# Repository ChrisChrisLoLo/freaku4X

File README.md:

# freaku4X

A 4x10 ortho keyboard with a knob and OLED. It embraces the excess minimalism of the key count, and embraces the excess extravagence of a knob and oled screen. It also has a lower profile than your typical 4x10 orthos, since the microcontroller is facing upwards rather than downwards.

## Status
Prototyping phase. While possible to print and use right now, a few refinements can be made.
Right now, the knob button needs to be placed on the key matrix, and I would prefer to rotate the keys around so that hotswap is southfacing.

With that said, this keyboard in it's current form is usable with some amount of tinkering

## Acknowledgements
Thank you to [PCBWay](https://www.pcbway.com/) for allowing me to experiment and create wild board designs that I wouldn't be able to prototype without their support. PCBWay has always been super friendly with their service, and the quality of thier boards are great, so I do recommend using their services. The've also been supporting the custom pcb keyboard community for a while, allowing for the hobby to continue to flourish.

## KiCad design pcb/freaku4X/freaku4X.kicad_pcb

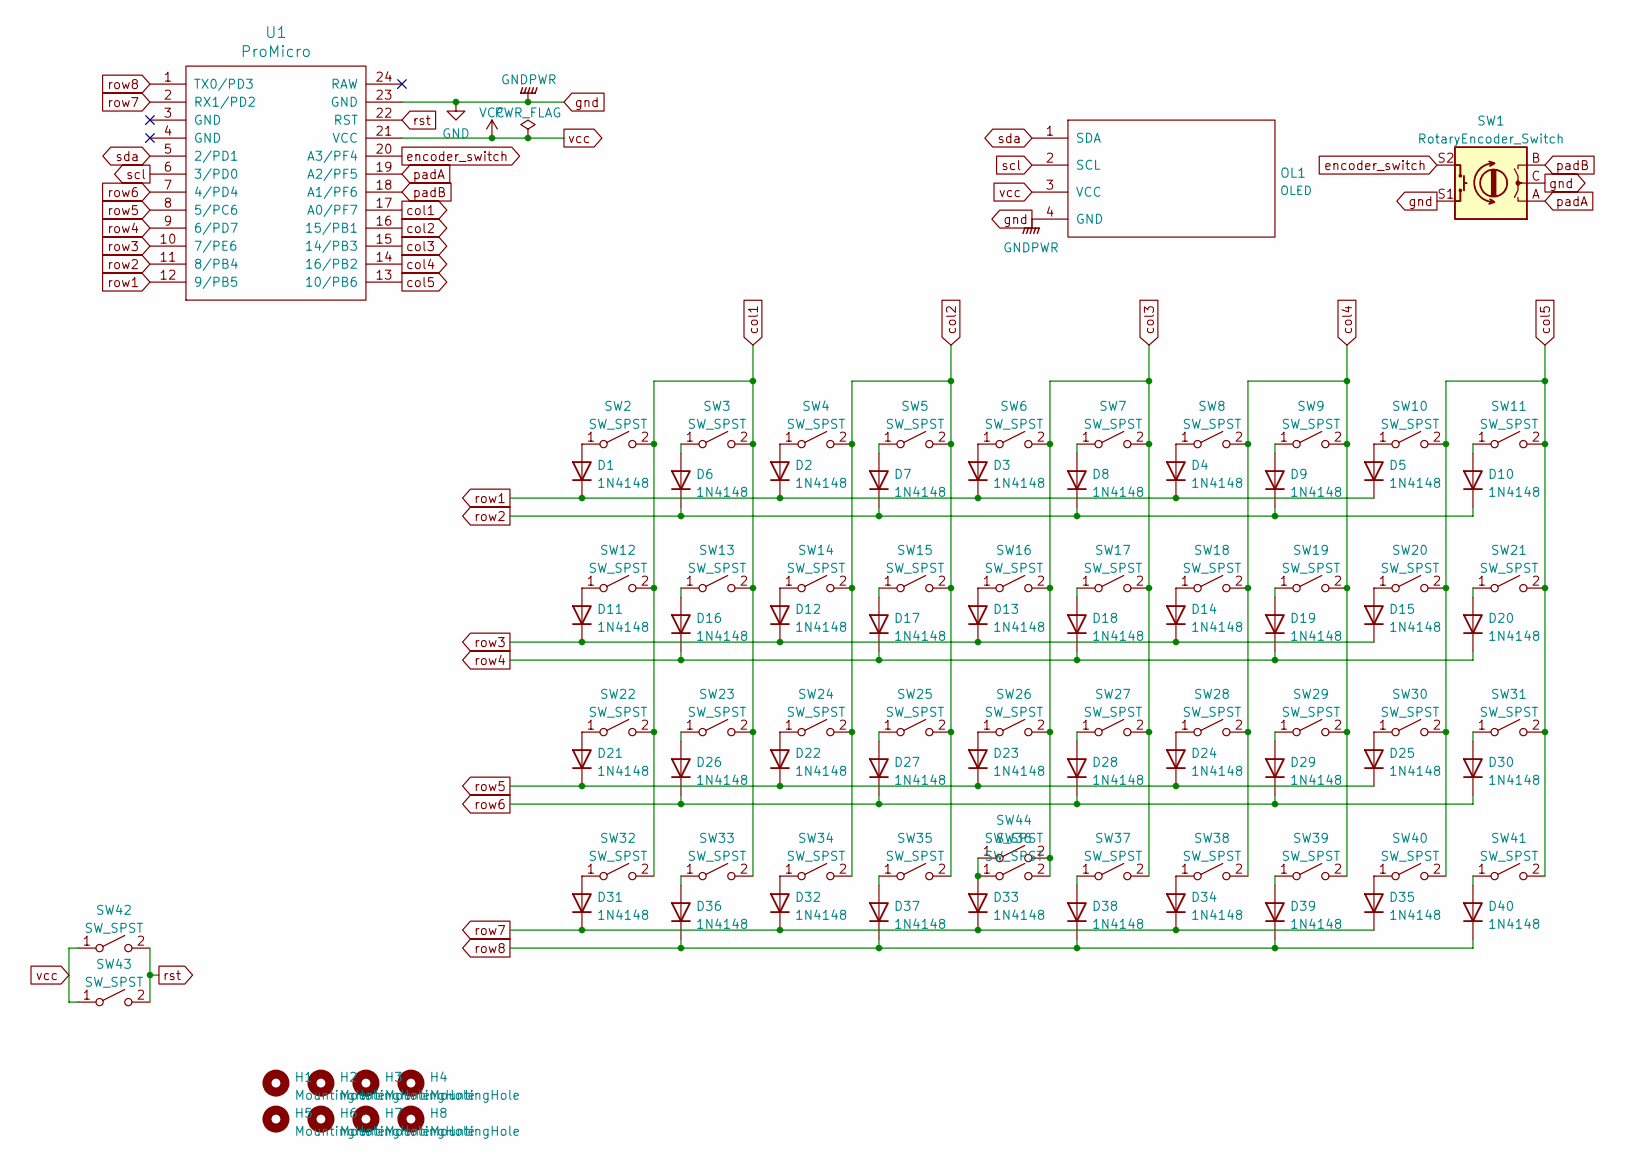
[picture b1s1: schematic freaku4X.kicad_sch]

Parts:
D1, D2, D3, D4, D5, D6, D7, D8, D9, D10, D11, D12, D13, D14, D15, D16, D17, D18, D19, D20, D21, D22, D23, D24, D25, D26, D27, D28, D29, D30, D31, D32, D33, D34, D35, D36, D37, D38, D39, D40: 1N4148
H1, H2, H3, H4, H5, H6, H7, H8: MountingHole; MountingHole_2.2mm_M2
OL1: OLED; OLED_v2
SW1: RotaryEncoder_Switch; RotaryEncoder_Alps_EC11E-Switch_Vertical_H20mm
SW2, SW3, SW4, SW5, SW6, SW7, SW8, SW9, SW10, SW11, SW12, SW13, SW14, SW15, SW16, SW17, SW18, SW19, SW20, SW21, SW22, SW23, SW24, SW25, SW26, SW27, SW28, SW29, SW30, SW31, SW32, SW33, SW34, SW35, SW36, SW37, SW38, SW39, SW40, SW41: SW_SPST; Kailh_socket_MX_optional
SW42: SW_SPST; ResetSW_4
SW43: SW_SPST; ResetSW
SW44: SW_SPST; SW_MX
U1: ProMicro; ProMicro_v3

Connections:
unnamed: D1.2 (A), SW2.1 (A)
unnamed: D2.2 (A), SW4.1 (A)
unnamed: D3.2 (A), SW6.1 (A)
unnamed: D4.2 (A), SW8.1 (A)
unnamed: D5.2 (A), SW10.1 (A)
unnamed: D6.2 (A), SW3.1 (A)
unnamed: D7.2 (A), SW5.1 (A)
unnamed: D8.2 (A), SW7.1 (A)
unnamed: D9.2 (A), SW9.1 (A)
unnamed: D10.2 (A), SW11.1 (A)
unnamed: D11.2 (A), SW12.1 (A)
unnamed: D12.2 (A), SW14.1 (A)
unnamed: D13.2 (A), SW16.1 (A)
unnamed: D14.2 (A), SW18.1 (A)
unnamed: D15.2 (A), SW20.1 (A)
unnamed: D16.2 (A), SW13.1 (A)
unnamed: D17.2 (A), SW15.1 (A)
unnamed: D18.2 (A), SW17.1 (A)
unnamed: D19.2 (A), SW19.1 (A)
unnamed: D20.2 (A), SW21.1 (A)
unnamed: D21.2 (A), SW22.1 (A)
unnamed: D22.2 (A), SW24.1 (A)
unnamed: D23.2 (A), SW26.1 (A)
unnamed: D24.2 (A), SW28.1 (A)
unnamed: D25.2 (A), SW30.1 (A)
unnamed: D26.2 (A), SW23.1 (A)
unnamed: D27.2 (A), SW25.1 (A)
unnamed: D28.2 (A), SW27.1 (A)
unnamed: D29.2 (A), SW29.1 (A)
unnamed: D30.2 (A), SW31.1 (A)
unnamed: D31.2 (A), SW32.1 (A)
unnamed: D32.2 (A), SW34.1 (A)
unnamed: D33.2 (A), SW36.1 (A), SW44.1 (A)
unnamed: D34.2 (A), SW38.1 (A)
unnamed: D35.2 (A), SW40.1 (A)
unnamed: D36.2 (A), SW33.1 (A)
unnamed: D37.2 (A), SW35.1 (A)
unnamed: D38.2 (A), SW37.1 (A)
unnamed: D39.2 (A), SW39.1 (A)
unnamed: D40.2 (A), SW41.1 (A)
col1: SW2.2 (B), SW3.2 (B), SW12.2 (B), SW13.2 (B), SW22.2 (B), SW23.2 (B), SW32.2 (B), SW33.2 (B), U1.17 (A0/PF7)
col2: SW4.2 (B), SW5.2 (B), SW14.2 (B), SW15.2 (B), SW24.2 (B), SW25.2 (B), SW34.2 (B), SW35.2 (B), U1.16 (15/PB1)
col3: SW6.2 (B), SW7.2 (B), SW16.2 (B), SW17.2 (B), SW26.2 (B), SW27.2 (B), SW36.2 (B), SW37.2 (B), SW44.2 (B), U1.15 (14/PB3)
col4: SW8.2 (B), SW9.2 (B), SW18.2 (B), SW19.2 (B), SW28.2 (B), SW29.2 (B), SW38.2 (B), SW39.2 (B), U1.14 (16/PB2)
col5: SW10.2 (B), SW11.2 (B), SW20.2 (B), SW21.2 (B), SW30.2 (B), SW31.2 (B), SW40.2 (B), SW41.2 (B), U1.13 (10/PB6)
encoder_switch: SW1.S2, U1.20 (A3/PF4)
gnd: OL1.4 (GND), SW1.C, SW1.S1, U1.23 (GND)
padA: SW1.A, U1.19 (A2/PF5)
padB: SW1.B, U1.18 (A1/PF6)
row1: D1.1 (K), D2.1 (K), D3.1 (K), D4.1 (K), D5.1 (K), U1.12 (9/PB5)
row2: D6.1 (K), D7.1 (K), D8.1 (K), D9.1 (K), D10.1 (K), U1.11 (8/PB4)
row3: D11.1 (K), D12.1 (K), D13.1 (K), D14.1 (K), D15.1 (K), U1.10 (7/PE6)
row4: D16.1 (K), D17.1 (K), D18.1 (K), D19.1 (K), D20.1 (K), U1.9 (6/PD7)
row5: D21.1 (K), D22.1 (K), D23.1 (K), D24.1 (K), D25.1 (K), U1.8 (5/PC6)
row6: D26.1 (K), D27.1 (K), D28.1 (K), D29.1 (K), D30.1 (K), U1.7 (4/PD4)
row7: D31.1 (K), D32.1 (K), D33.1 (K), D34.1 (K), D35.1 (K), U1.2 (RX1/PD2)
row8: D36.1 (K), D37.1 (K), D38.1 (K), D39.1 (K), D40.1 (K), U1.1 (TX0/PD3)
rst: SW42.2 (B), SW43.2 (B), U1.22 (RST)
scl: OL1.2 (SCL), U1.6 (3/PD0)
sda: OL1.1 (SDA), U1.5 (2/PD1)
vcc: OL1.3 (VCC), SW42.1 (A), SW43.1 (A), U1.21 (VCC)

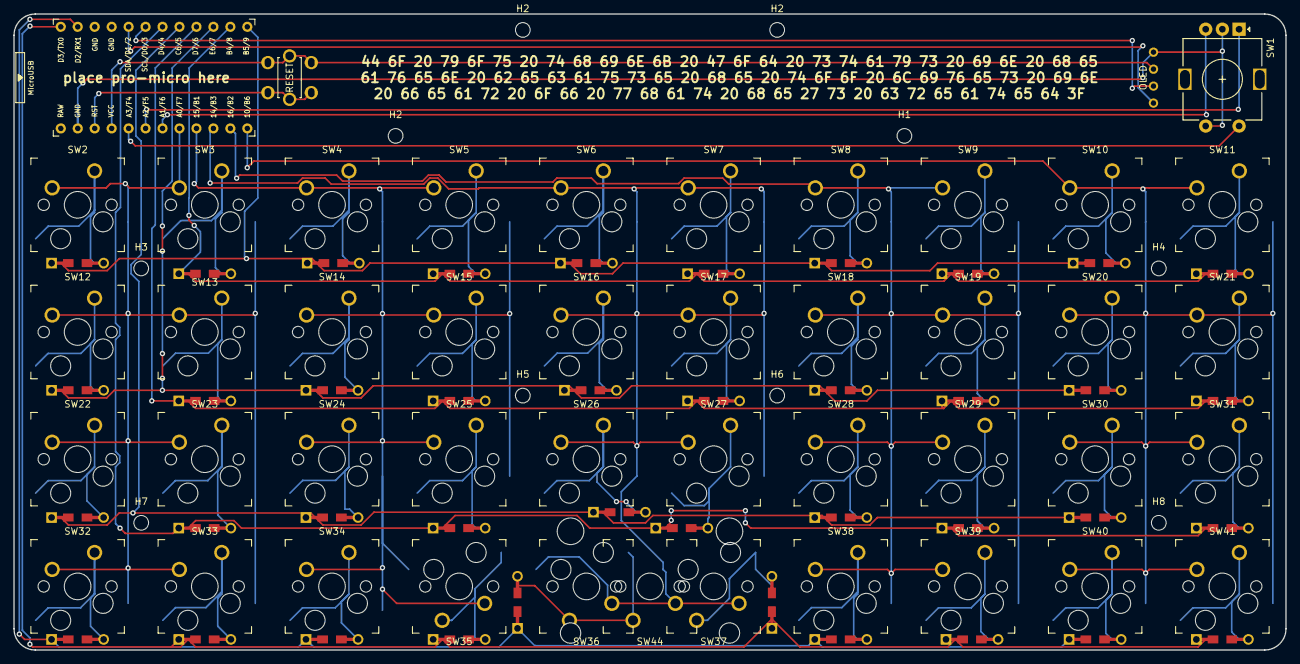
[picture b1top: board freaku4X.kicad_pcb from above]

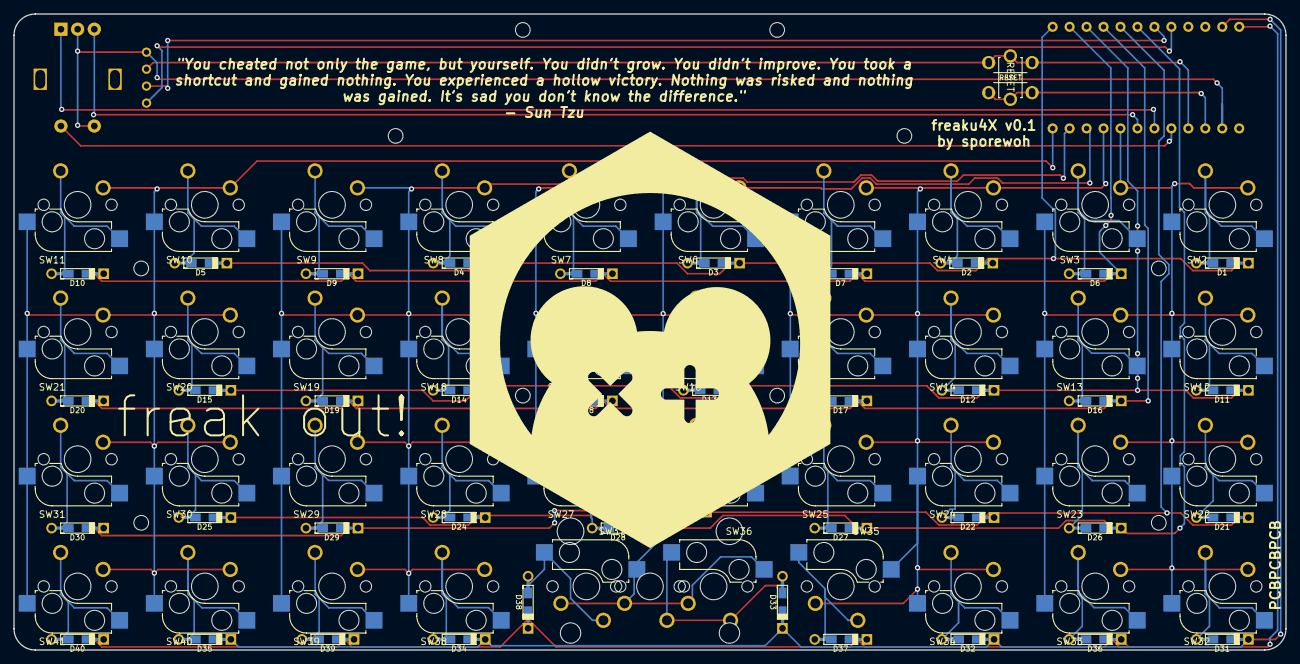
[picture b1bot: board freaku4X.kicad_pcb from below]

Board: 2 copper layers, 190.5 x 95.2 mm, 96 parts (41 on the bottom side), 61 nets.

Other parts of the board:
H2#2, H2#3: MountingHole; MountingHole_2.2mm_M2

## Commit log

2022-04-17 init project
2022-04-18 complete schematic
2022-04-21 finish first iteration of PCB
2022-05-09 add gerbers
2022-05-28 add vial firmware
2022-05-28 add image
